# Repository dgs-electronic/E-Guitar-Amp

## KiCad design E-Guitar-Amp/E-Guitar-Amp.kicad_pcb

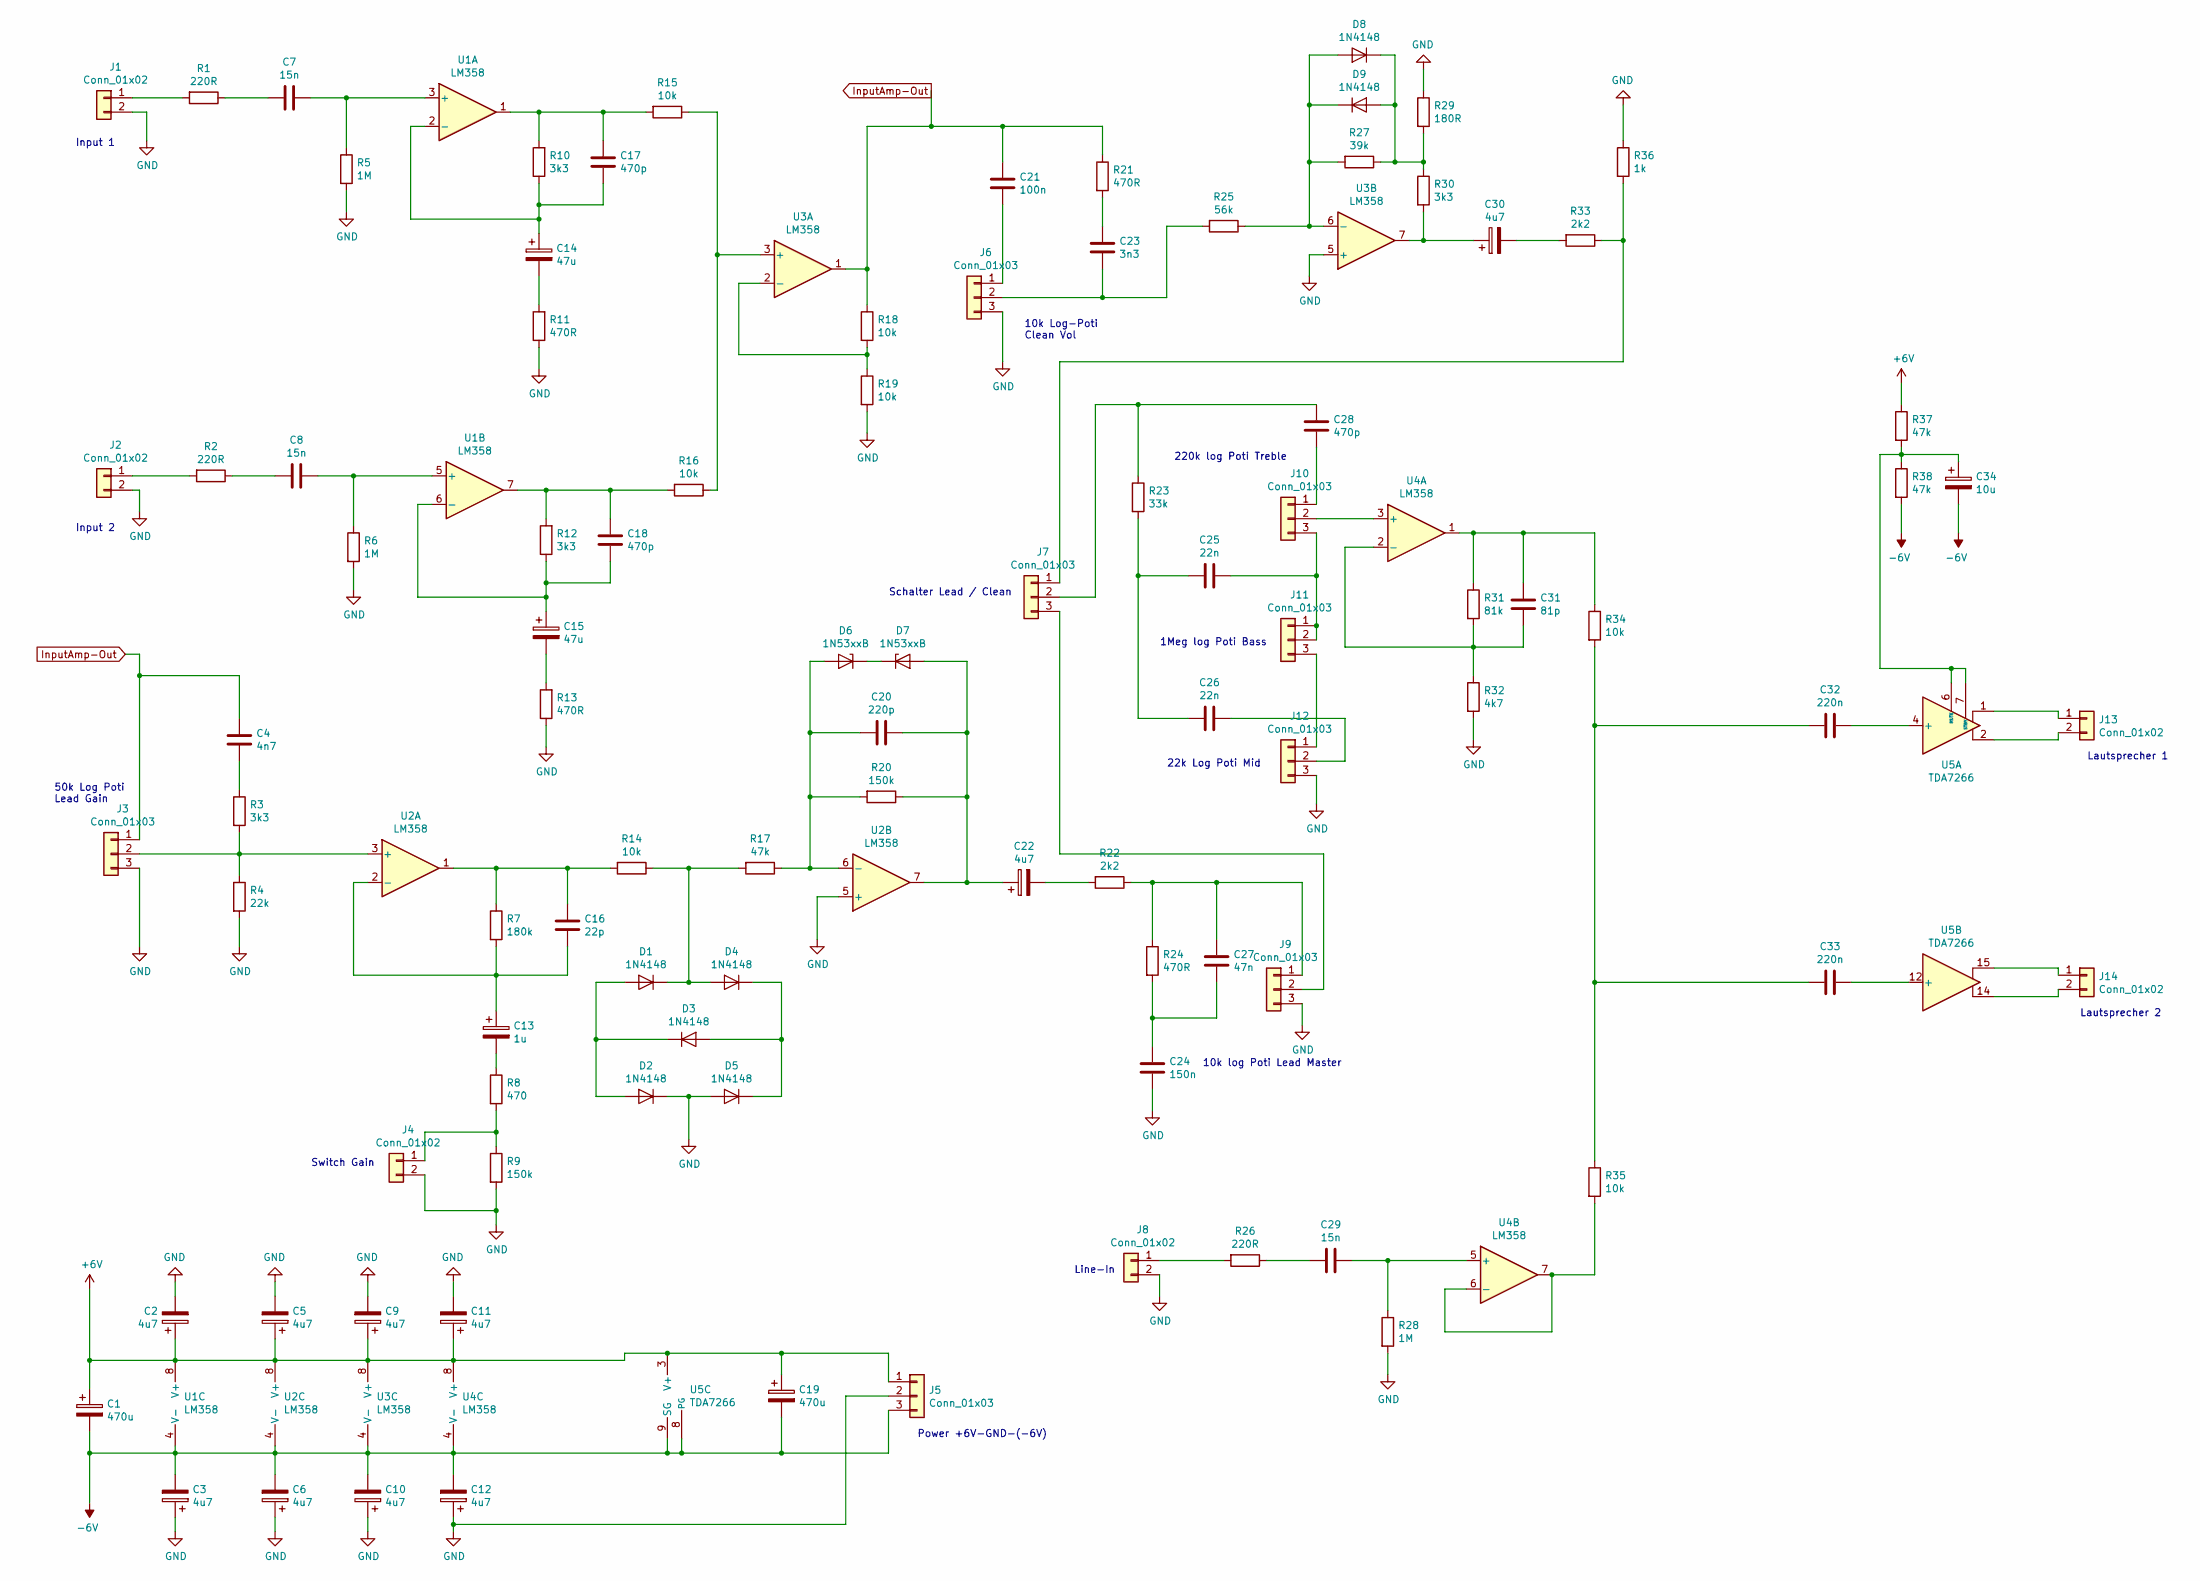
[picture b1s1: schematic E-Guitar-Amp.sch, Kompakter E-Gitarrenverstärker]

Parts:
C1, C19: 470u; CP_Radial_D10.0mm_P5.00mm
C2, C3, C5, C6, C9, C10, C11, C12, C22, C30: 4u7; CP_Radial_D4.0mm_P1.50mm
C4: 4n7; C_Disc_D5.0mm_W2.5mm_P2.50mm
C7, C8, C29: 15n; C_Disc_D7.5mm_W2.5mm_P5.00mm
C13: 1u; C_Disc_D5.0mm_W2.5mm_P2.50mm
C14, C15: 47u; CP_Radial_D5.0mm_P2.00mm
C16: 22p; C_Disc_D3.4mm_W2.1mm_P2.50mm
C17, C18, C28: 470p; C_Disc_D5.0mm_W2.5mm_P2.50mm
C20: 220p; C_Disc_D5.0mm_W2.5mm_P2.50mm
C21: 100n; C_Disc_D7.5mm_W2.5mm_P5.00mm
C23: 3n3; C_Disc_D5.0mm_W2.5mm_P2.50mm
C24: 150n; C_Disc_D7.5mm_W2.5mm_P5.00mm
C25, C26: 22n; C_Disc_D7.5mm_W2.5mm_P5.00mm
C27: 47n; C_Disc_D7.5mm_W2.5mm_P5.00mm
C31: 81p; C_Disc_D3.4mm_W2.1mm_P2.50mm
C32, C33: 220n; C_Disc_D7.5mm_W5.0mm_P5.00mm
C34: 10u; CP_Radial_D6.3mm_P2.50mm
D1, D2, D3, D4, D5, D8, D9: 1N4148; D_DO-35_SOD27_P7.62mm_Horizontal
D6, D7: 1N53xxB; D_DO-35_SOD27_P7.62mm_Horizontal
J1, J2, J4, J8, J13, J14: Conn_01x02; Pin_Header_Straight_1x02_Pitch2.54mm
J3, J5, J6, J7, J9, J10, J11, J12: Conn_01x03; Pin_Header_Straight_1x03_Pitch2.54mm
R1, R2, R26: 220R; R_Axial_DIN0207_L6.3mm_D2.5mm_P10.16mm_Horizontal
R3, R10, R12, R30: 3k3; R_Axial_DIN0207_L6.3mm_D2.5mm_P10.16mm_Horizontal
R4: 22k; R_Axial_DIN0207_L6.3mm_D2.5mm_P10.16mm_Horizontal
R5, R6, R28: 1M; R_Axial_DIN0207_L6.3mm_D2.5mm_P10.16mm_Horizontal
R7: 180k; R_Axial_DIN0207_L6.3mm_D2.5mm_P10.16mm_Horizontal
R8: 470; R_Axial_DIN0207_L6.3mm_D2.5mm_P10.16mm_Horizontal
R9, R20: 150k; R_Axial_DIN0207_L6.3mm_D2.5mm_P10.16mm_Horizontal
R11, R13, R21, R24: 470R; R_Axial_DIN0207_L6.3mm_D2.5mm_P10.16mm_Horizontal
R14, R15, R16, R18, R19, R34, R35: 10k; R_Axial_DIN0207_L6.3mm_D2.5mm_P10.16mm_Horizontal
R17, R37, R38: 47k; R_Axial_DIN0207_L6.3mm_D2.5mm_P10.16mm_Horizontal
R22, R33: 2k2; R_Axial_DIN0207_L6.3mm_D2.5mm_P10.16mm_Horizontal
R23: 33k; R_Axial_DIN0207_L6.3mm_D2.5mm_P10.16mm_Horizontal
R25: 56k; R_Axial_DIN0207_L6.3mm_D2.5mm_P10.16mm_Horizontal
R27: 39k; R_Axial_DIN0207_L6.3mm_D2.5mm_P10.16mm_Horizontal
R29: 180R; R_Axial_DIN0207_L6.3mm_D2.5mm_P10.16mm_Horizontal
R31: 81k; R_Axial_DIN0207_L6.3mm_D2.5mm_P10.16mm_Horizontal
R32: 4k7; R_Axial_DIN0207_L6.3mm_D2.5mm_P10.16mm_Horizontal
R36: 1k; R_Axial_DIN0207_L6.3mm_D2.5mm_P10.16mm_Horizontal
U1, U2, U3, U4: LM358; DIP-8_W7.62mm_Socket_LongPads
U5: TDA7266; TO-220-15_Vertical_StaggeredType1

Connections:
+6V: C1.1, C2.1, C5.1, C9.1, C11.1, C19.1, J5.1, R37.1, U1.8 (V+), U2.8 (V+), U3.8 (V+), U4.8 (V+), U5.3 (V+), U5.13 (V+)
-6V: C1.2, C3.2, C6.2, C10.2, C12.2, C19.2, C34.2, J5.3, R38.2, U1.4 (V-), U2.4 (V-), U3.4 (V-), U4.4 (V-), U5.8 (PG), U5.9 (SG)
GND: C2.2, C3.1, C5.2, C6.1, C9.2, C10.1, C11.2, C12.1, C24.2, D2.1 (K), D5.2 (A), J1.2, J2.2, J3.3, J4.2, J5.2, J6.3, J8.2, J9.3, J12.3, R4.2, R5.2, R6.2, R9.2, R11.1, R13.1, R19.2, R28.2, R29.1, R32.2, R36.1, U2.5 (+), U3.5 (+)
InputAmp-Out: C4.1, C21.1, J3.1, R18.1, R21.1, U3.1
unnamed: C4.2, R3.1
unnamed: C7.1, R5.1, U1.3 (+)
unnamed: C7.2, R1.1
unnamed: C8.1, R6.1, U1.5 (+)
unnamed: C8.2, R2.1
unnamed: C13.1, C16.2, R7.2, U2.2 (-)
unnamed: C13.2, R8.1
unnamed: C14.1, C17.1, R10.1, U1.2 (-)
unnamed: C14.2, R11.2
unnamed: C15.1, C18.1, R12.1, U1.6 (-)
unnamed: C15.2, R13.2
unnamed: C16.1, R7.1, R14.2, U2.1
unnamed: C17.2, R10.2, R15.2, U1.1
unnamed: C18.2, R12.2, R16.2, U1.7
unnamed: C20.1, C22.1, D7.2 (A), R20.1, U2.7
unnamed: C20.2, D6.2 (A), R17.1, R20.2, U2.6 (-)
unnamed: C21.2, J6.1
unnamed: C22.2, R22.2
unnamed: C23.1, R21.2
unnamed: C23.2, J6.2, R25.2
unnamed: C24.1, C27.2, R24.2
unnamed: C25.1, J10.3, J11.1, J11.2
unnamed: C25.2, C26.2, R23.2
unnamed: C26.1, J12.2
unnamed: C27.1, J9.1, R22.1, R24.1
unnamed: C28.1, J7.2, R23.1
unnamed: C28.2, J10.1
unnamed: C29.1, R28.1, U4.5 (+)
unnamed: C29.2, R26.1
unnamed: C30.1, R30.2, U3.7
unnamed: C30.2, R33.2
unnamed: C31.1, R31.1, R34.1, U4.1
unnamed: C31.2, R31.2, R32.1, U4.2 (-)
unnamed: C32.1, U5.4 (+)
unnamed: C32.2, C33.2, R34.2, R35.1
unnamed: C33.1, U5.12 (+)
unnamed: C34.1, R37.2, R38.1, U5.6 (MUTE), U5.7 (STBY)
unnamed: D1.1 (K), D4.2 (A), R14.1, R17.2
unnamed: D1.2 (A), D2.2 (A), D3.1 (K)
unnamed: D3.2 (A), D4.1 (K), D5.1 (K)
unnamed: D6.1 (K), D7.1 (K)
unnamed: D8.1 (K), D9.2 (A), R27.1, R29.2, R30.1
unnamed: D8.2 (A), D9.1 (K), R25.1, R27.2, U3.6 (-)
unnamed: J1.1, R1.2
unnamed: J2.1, R2.2
unnamed: J3.2, R3.2, R4.1, U2.3 (+)
unnamed: J4.1, R8.2, R9.1
unnamed: J7.1, R33.1, R36.2
unnamed: J7.3, J9.2
unnamed: J8.1, R26.2
unnamed: J10.2, U4.3 (+)
unnamed: J11.3, J12.1
unnamed: J13.1, U5.1
unnamed: J13.2, U5.2
unnamed: J14.1, U5.15
unnamed: J14.2, U5.14
unnamed: R15.1, R16.1, U3.3 (+)
unnamed: R18.2, R19.1, U3.2 (-)
unnamed: R35.2, U4.6 (-), U4.7

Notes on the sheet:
Input 1
Input 2
10k Log-Poti Clean Vol
Switch Gain
50k Log Poti Lead Gain
10k log Poti Lead Master
220k log Poti Treble
1Meg log Poti Bass
22k Log Poti Mid
Schalter Lead / Clean
Line-In
Lautsprecher 1
Lautsprecher 2
Power +6V-GND-(-6V)

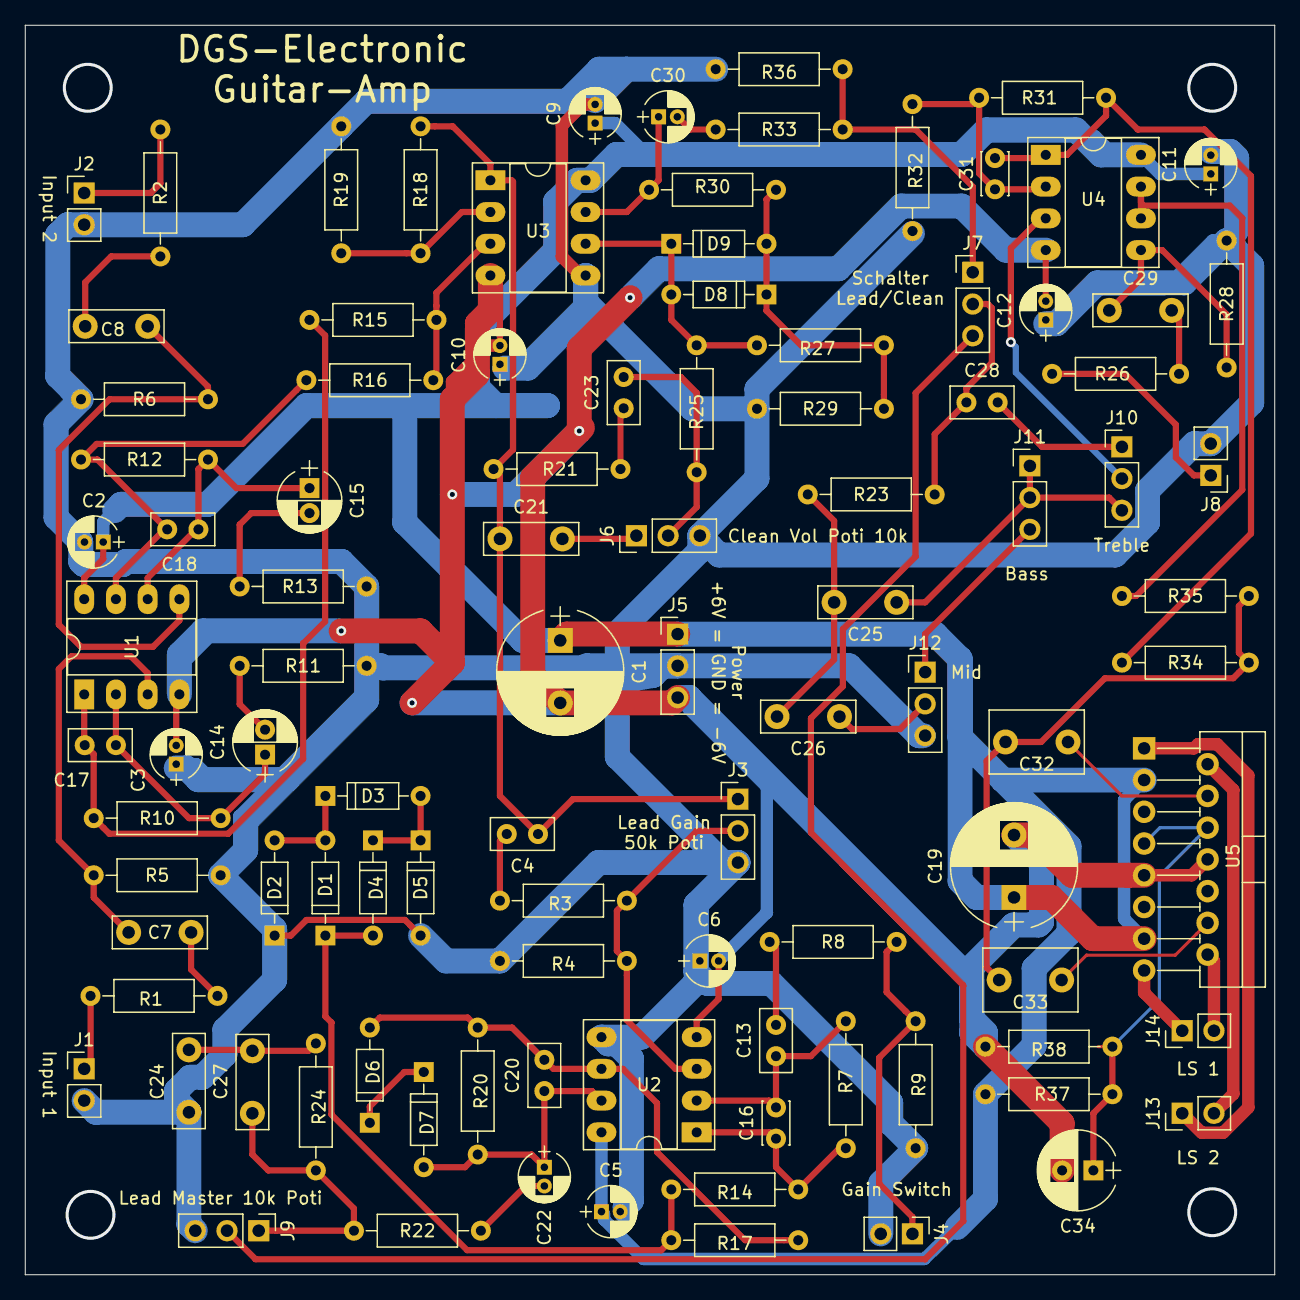
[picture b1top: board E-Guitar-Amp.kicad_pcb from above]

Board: 2 copper layers, 100.0 x 100.0 mm, 100 parts (0 on the bottom side), 63 nets.

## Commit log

2020-01-01 Files checked in
